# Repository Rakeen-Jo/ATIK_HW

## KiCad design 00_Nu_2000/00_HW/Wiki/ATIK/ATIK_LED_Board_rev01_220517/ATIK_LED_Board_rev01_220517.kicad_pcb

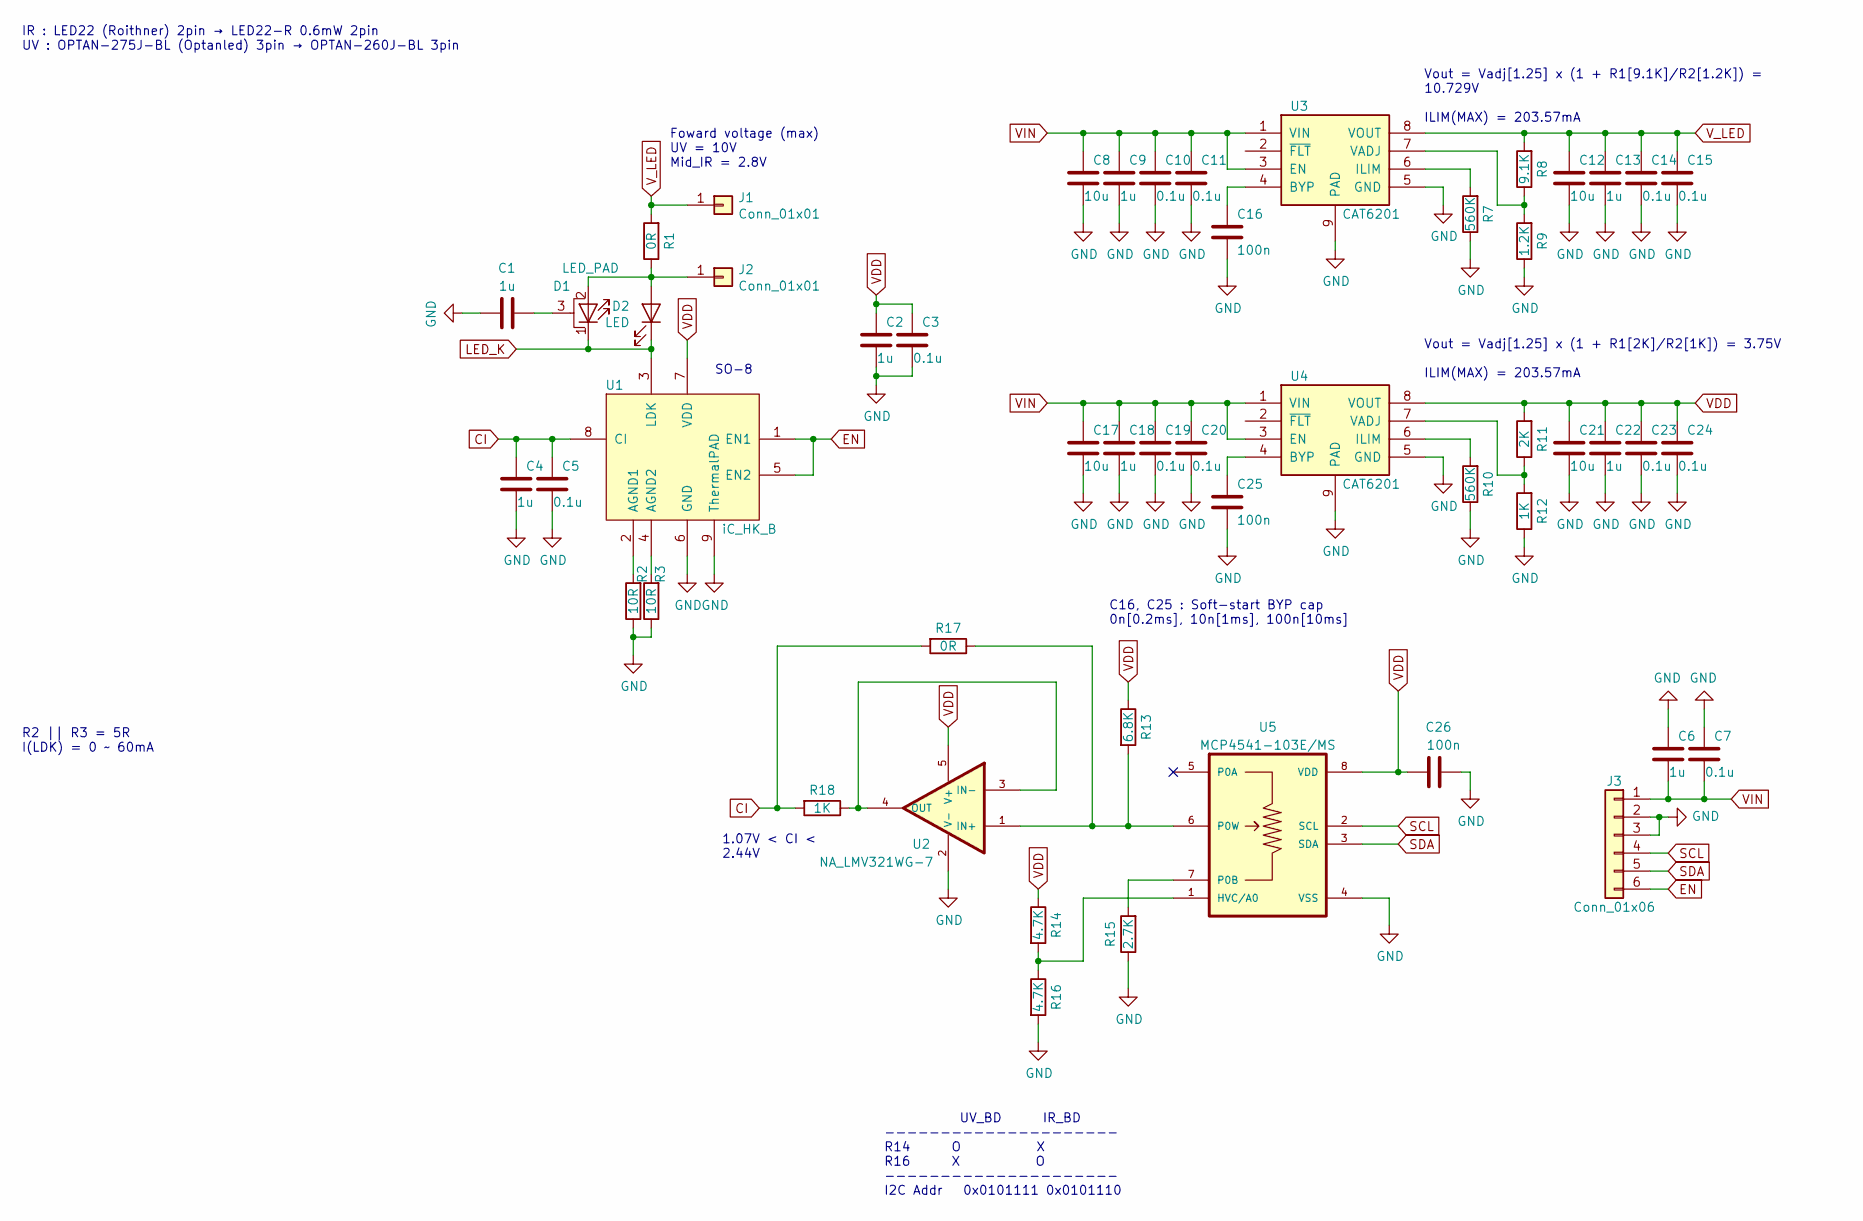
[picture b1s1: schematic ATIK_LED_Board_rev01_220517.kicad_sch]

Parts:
C1, C2, C4, C6, C9, C13, C18, C22: 1u; C_0603_1608Metric
C3, C5, C7, C10, C11, C14, C15, C19, C20, C23, C24: 0.1u; C_0603_1608Metric
C8, C12, C17, C21: 10u; C_1206_3216Metric
C16, C25, C26: 100n; C_0603_1608Metric
D1: LED_PAD; LED_D5.0mm
D2: LED; LED_D5.0mm
J1, J2: Conn_01x01; Pin_Header_Straight_1x01_Pitch2.54mm
J3: Conn_01x06; 5268-06A
R1, R17: 0R; R_0603_1608Metric
R2, R3: 10R; R_0603_1608Metric
R7, R10: 560K; R_0603_1608Metric
R8: 9.1K; R_0603_1608Metric
R9: 1.2K; R_0603_1608Metric
R11: 2K; R_0603_1608Metric
R12, R18: 1K; R_0603_1608Metric
R13: 6.8K; R_0805_2012Metric
R14, R16: 4.7K; R_0805_2012Metric
R15: 2.7K; R_0805_2012Metric
U1: iC_HK_B; SOIC-8-1EP_3.9x4.9mm_P1.27mm
U2: NA_LMV321WG-7; SOT95P285X145-5N
U3, U4: CAT6201; TDFN-8(ON semi)
U5: MCP4541-103E/MS; SOP65P490X110-8N

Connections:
CI: C4.1, C5.1, R17.2, R18.2, U1.8 (CI)
EN: J3.6, U1.1 (EN1), U1.5 (EN2)
GND: C1.1, C2.2, C3.2, C4.2, C5.2, C6.1, C7.1, C8.2, C9.2, C10.2, C11.2, C12.2, C13.2, C14.2, C15.2, C16.2, C17.2, C18.2, C19.2, C20.2, C21.2, C22.2, C23.2, C24.2, C25.2, C26.2, J3.2, J3.3, R2.1, R3.1, R7.1, R9.1, R10.1, R12.1, R15.1, R16.2, U1.6 (GND), U1.9 (ThermalPAD), U2.2 (V-), U3.5 (GND), U3.9 (PAD), U4.5 (GND), U4.9 (PAD), U5.4 (VSS)
LED_K: D1.1 (K), D2.1 (K), U1.3 (LDK)
unnamed: D1.2 (A), D2.2 (A), J2.1, R1.1
unnamed: C1.2, D1.3 (PAD)
unnamed: R2.2, U1.2 (AGND1)
unnamed: R3.2, U1.4 (AGND2)
unnamed: R13.2, R17.1, U2.1 (IN+), U5.6 (P0W)
unnamed: R18.1, U2.3 (IN-), U2.4 (OUT)
unnamed: C16.1, U3.4 (BYP)
unnamed: R7.2, U3.6 (ILIM)
unnamed: R8.1, R9.2, U3.7 (VADJ)
unnamed: C25.1, U4.4 (BYP)
unnamed: R10.2, U4.6 (ILIM)
unnamed: R11.1, R12.2, U4.7 (VADJ)
unnamed: R14.2, R16.1, U5.1 (HVC/A0)
unnamed: R15.2, U5.7 (P0B)
SCL: J3.4, U5.2 (SCL)
SDA: J3.5, U5.3 (SDA)
VDD: C2.1, C3.1, C21.1, C22.1, C23.1, C24.1, C26.1, R11.2, R13.1, R14.1, U1.7 (VDD), U2.5 (V+), U4.8 (VOUT), U5.8 (VDD)
VIN: C6.2, C7.2, C8.1, C9.1, C10.1, C11.1, C17.1, C18.1, C19.1, C20.1, J3.1, U3.1 (VIN), U3.3 (EN), U4.1 (VIN), U4.3 (EN)
V_LED: C12.1, C13.1, C14.1, C15.1, J1.1, R1.2, R8.2, U3.8 (VOUT)

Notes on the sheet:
C16, C25 : Soft-start BYP cap 0n[0.2ms], 10n[1ms], 100n[10ms]
Vout = Vadj[1.25] x (1 + R1[2K]/R2[1K]) = 3.75V ILIM(MAX) = 203.57mA
Vout = Vadj[1.25] x (1 + R1[9.1K]/R2[1.2K]) = 10.729V ILIM(MAX) = 203.57mA
1.07V < CI < 2.44V
UV_BD IR_BD --------------------- R14 O X R16 X O --------------------- I2C Addr 0x0101111 0x0101110
R2 || R3 = 5R I(LDK) = 0 ~ 60mA
Foward voltage (max) UV = 10V Mid_IR = 2.8V
IR : LED22 (Roithner) 2pin → LED22-R 0.6mW 2pin UV : OPTAN-275J-BL (Optanled) 3pin → OPTAN-260J-BL 3pin
SO-8

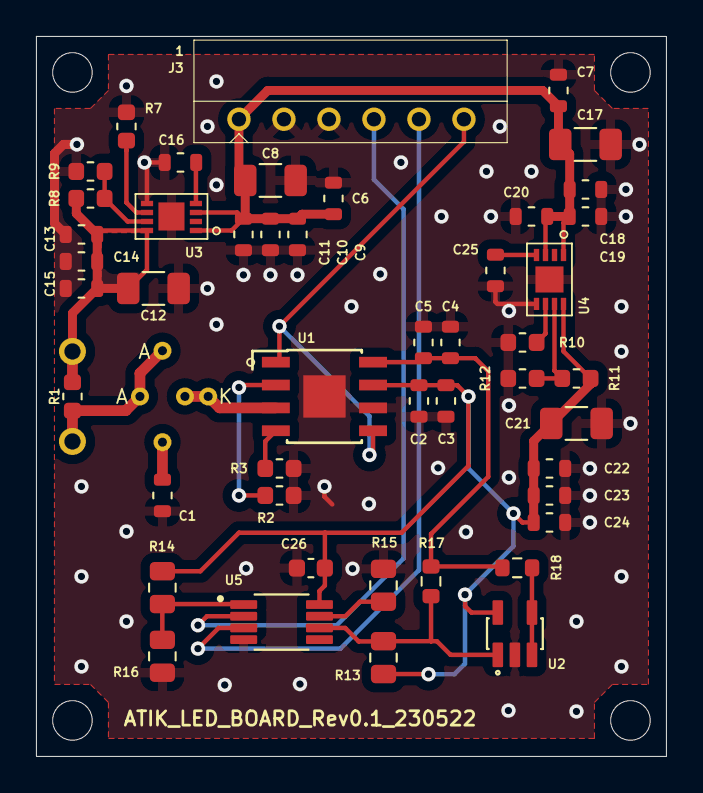
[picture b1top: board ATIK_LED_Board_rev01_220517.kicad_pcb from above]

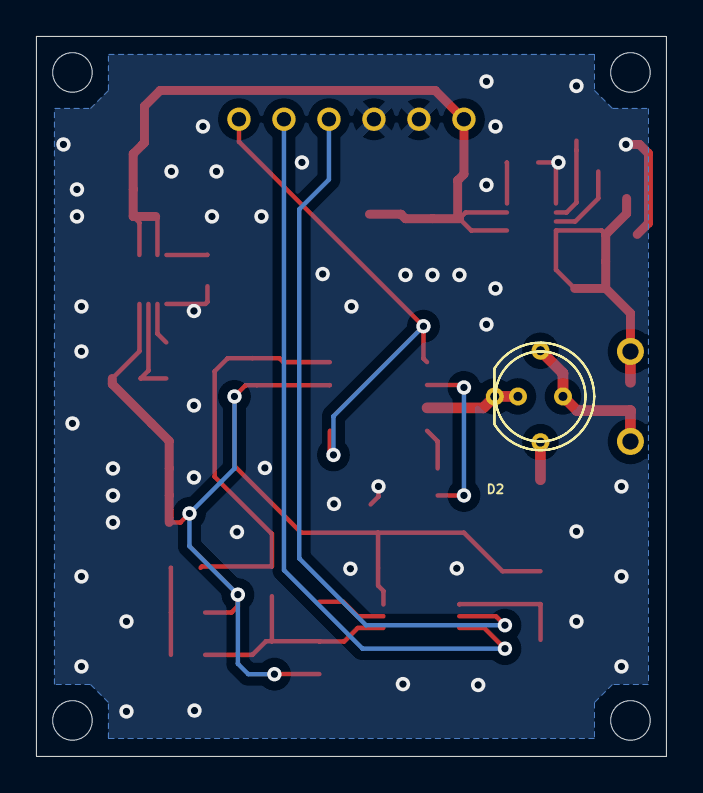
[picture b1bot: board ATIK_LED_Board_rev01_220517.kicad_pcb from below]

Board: 2 copper layers, 35.0 x 40.0 mm, 51 parts (2 on the bottom side), 23 nets.

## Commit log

2024-03-05 Backup
